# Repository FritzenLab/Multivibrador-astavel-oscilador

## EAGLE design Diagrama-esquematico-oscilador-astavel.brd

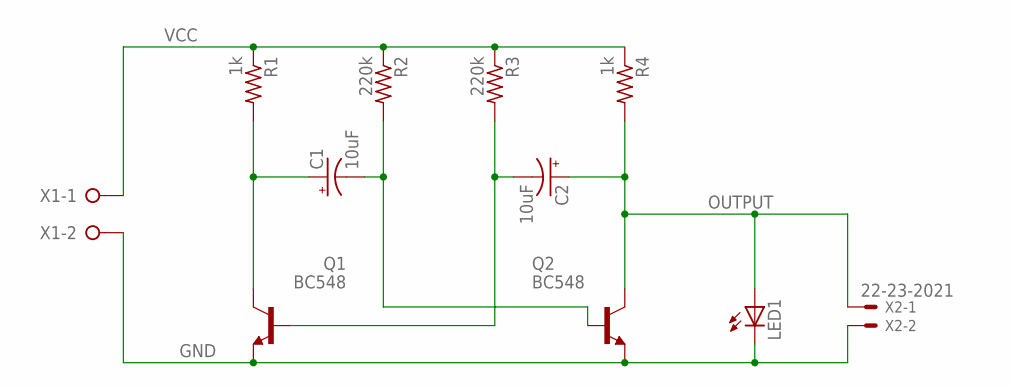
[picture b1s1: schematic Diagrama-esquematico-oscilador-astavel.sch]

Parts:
C1, C2: 10uF; E2-4
LED1: LED5MM
Q1, Q2: BC548; TO92-EBC
R1, R4: 1k; 0207/10
R2, R3: 220k; 0207/10
X1: W237-02P; W237-132
X2: 22-23-2021

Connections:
GND: LED1.K (C), Q1.E, Q2.E, X1.2, X2.2
unnamed: C2.-, Q1.B, R3.2
unnamed: C1.+, Q1.C, R1.2
unnamed: C1.-, Q2.B, R2.2
OUTPUT: C2.+, LED1.A, Q2.C, R4.2, X2.1
VCC: R1.1, R2.1, R3.1, R4.1, X1.1

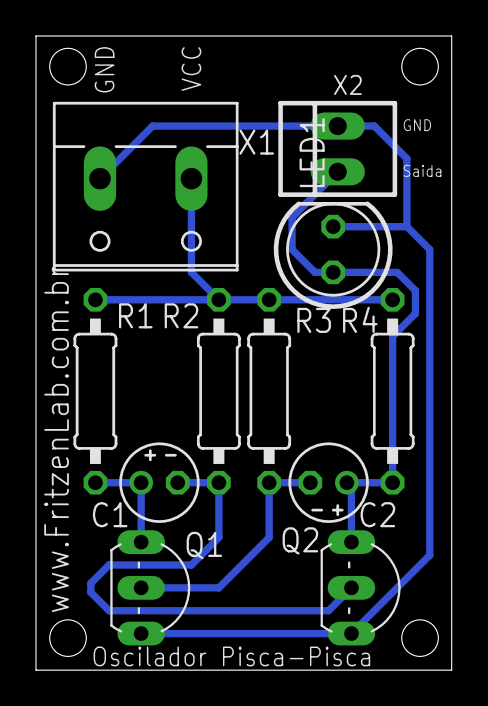
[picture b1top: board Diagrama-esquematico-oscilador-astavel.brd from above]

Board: 2 copper layers, 23.1 x 35.2 mm, 11 parts (0 on the bottom side), 6 nets.

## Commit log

2018-03-18 arquivos de design da PCB
